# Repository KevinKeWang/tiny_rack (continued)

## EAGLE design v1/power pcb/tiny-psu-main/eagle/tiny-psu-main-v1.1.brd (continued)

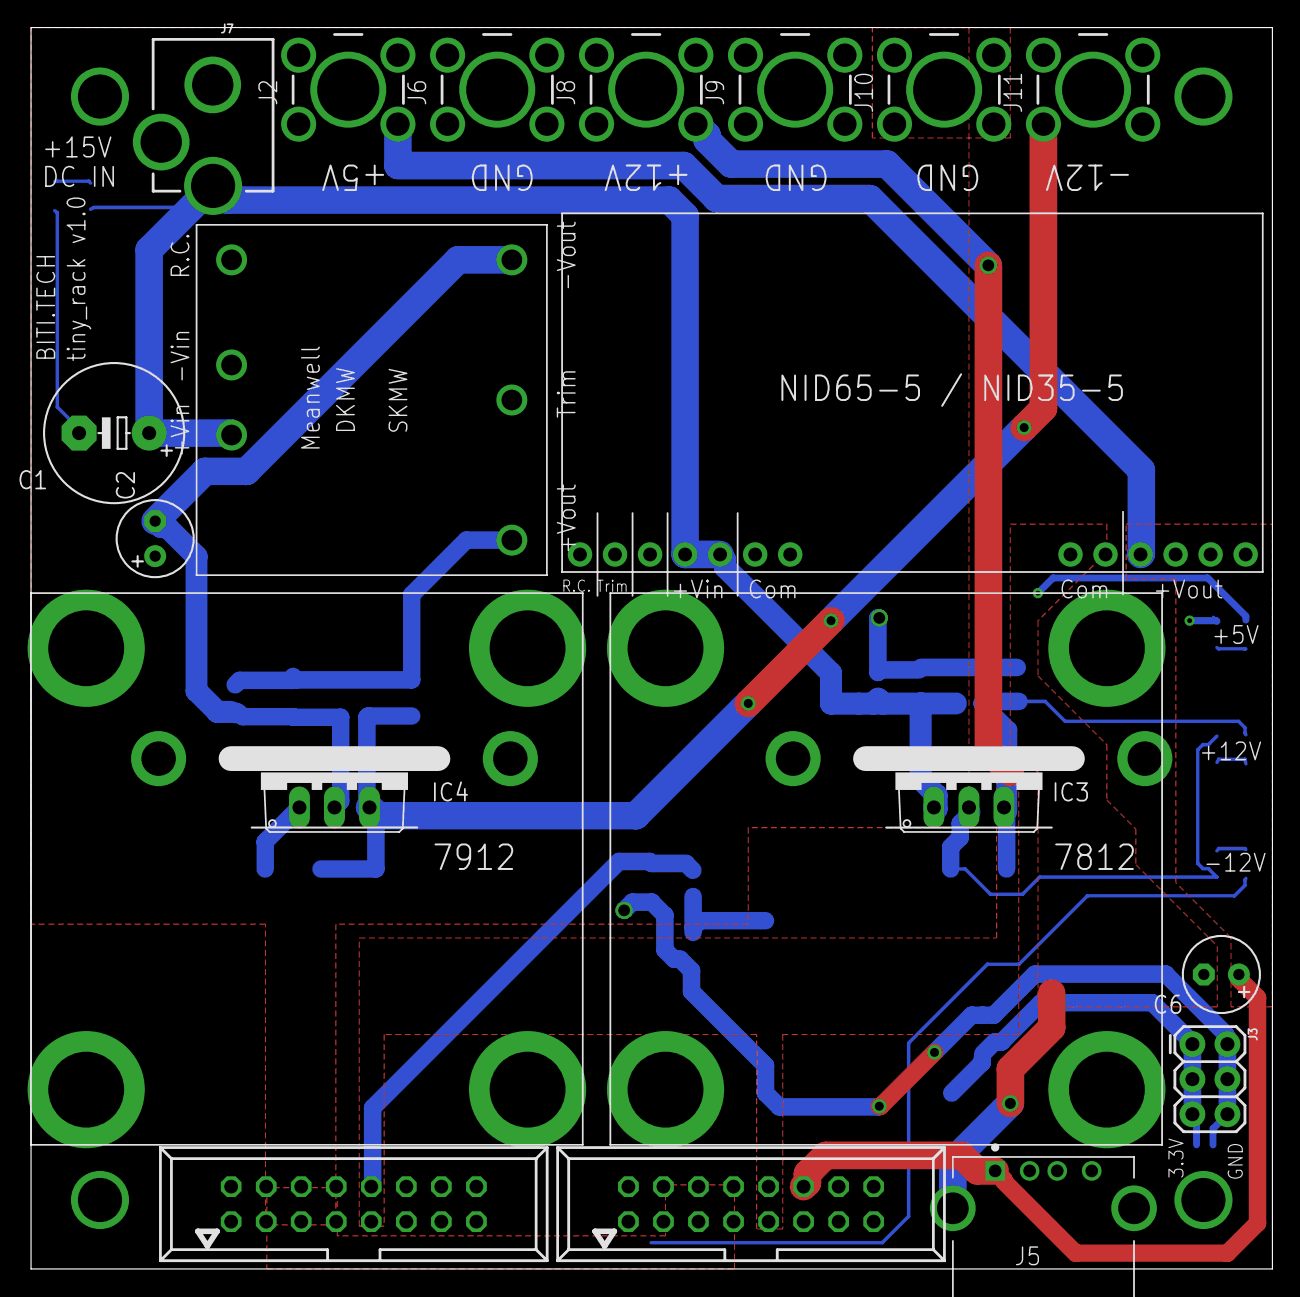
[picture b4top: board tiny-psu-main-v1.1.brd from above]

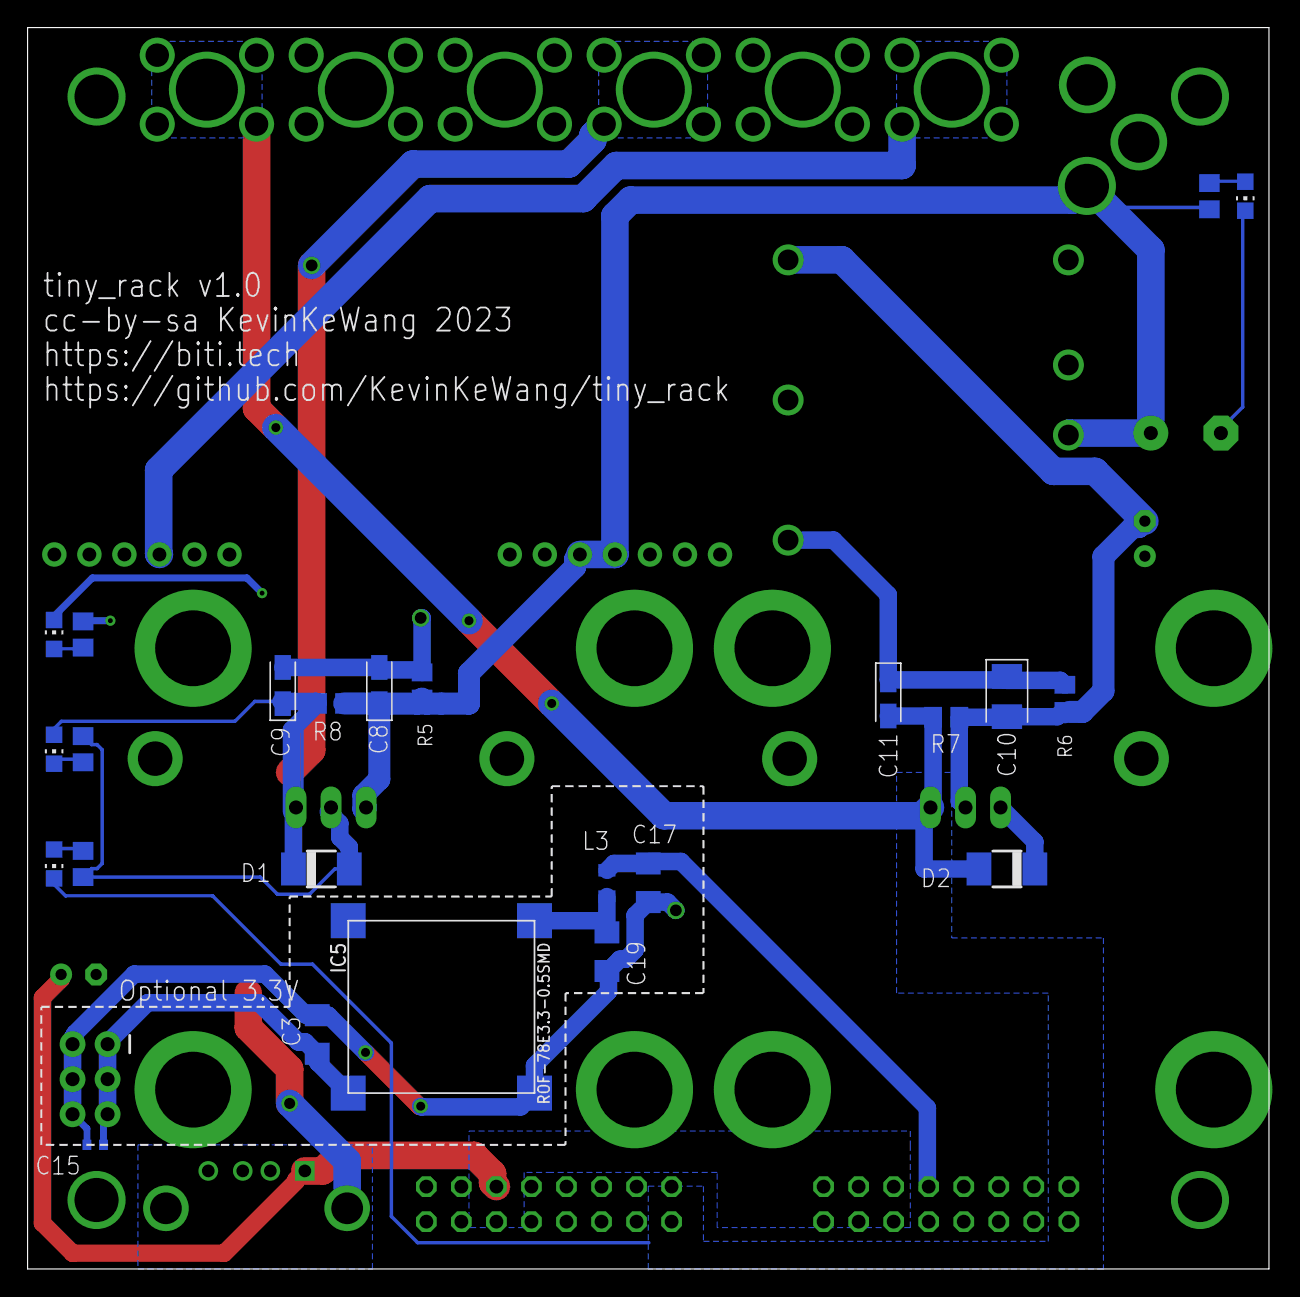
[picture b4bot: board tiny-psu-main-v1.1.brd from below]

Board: 4 copper layers, 90.0 x 90.0 mm, 46 parts (24 on the bottom side), 12 nets.

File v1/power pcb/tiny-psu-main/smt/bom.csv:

Comment,Designator,Footprint,jlc-partNo
LED,"LED1, LED2, LED3, LED4",0805,C2987021
1.2k,R3,0805,C17379
2.4k,"R1, R2, R4, R5, R6",0805,C17526
510R,"R7, R8",0805,C17734
100nF,C15,0402,C307331
22uF,"C3, C17, C19",1206,C12891
100nF,C9,CAPMP3216X180N,C7173
330nF,C8,CAPMP3216X180N,C8014
1uF,C11,CAPMP3216X180N,C7176
2.2uF,C10,CAPMP3528X210N,C19276
B360A-13-F,"D1, D2",DO-214AC,C94193
33uH,L3,L2012C,C383405

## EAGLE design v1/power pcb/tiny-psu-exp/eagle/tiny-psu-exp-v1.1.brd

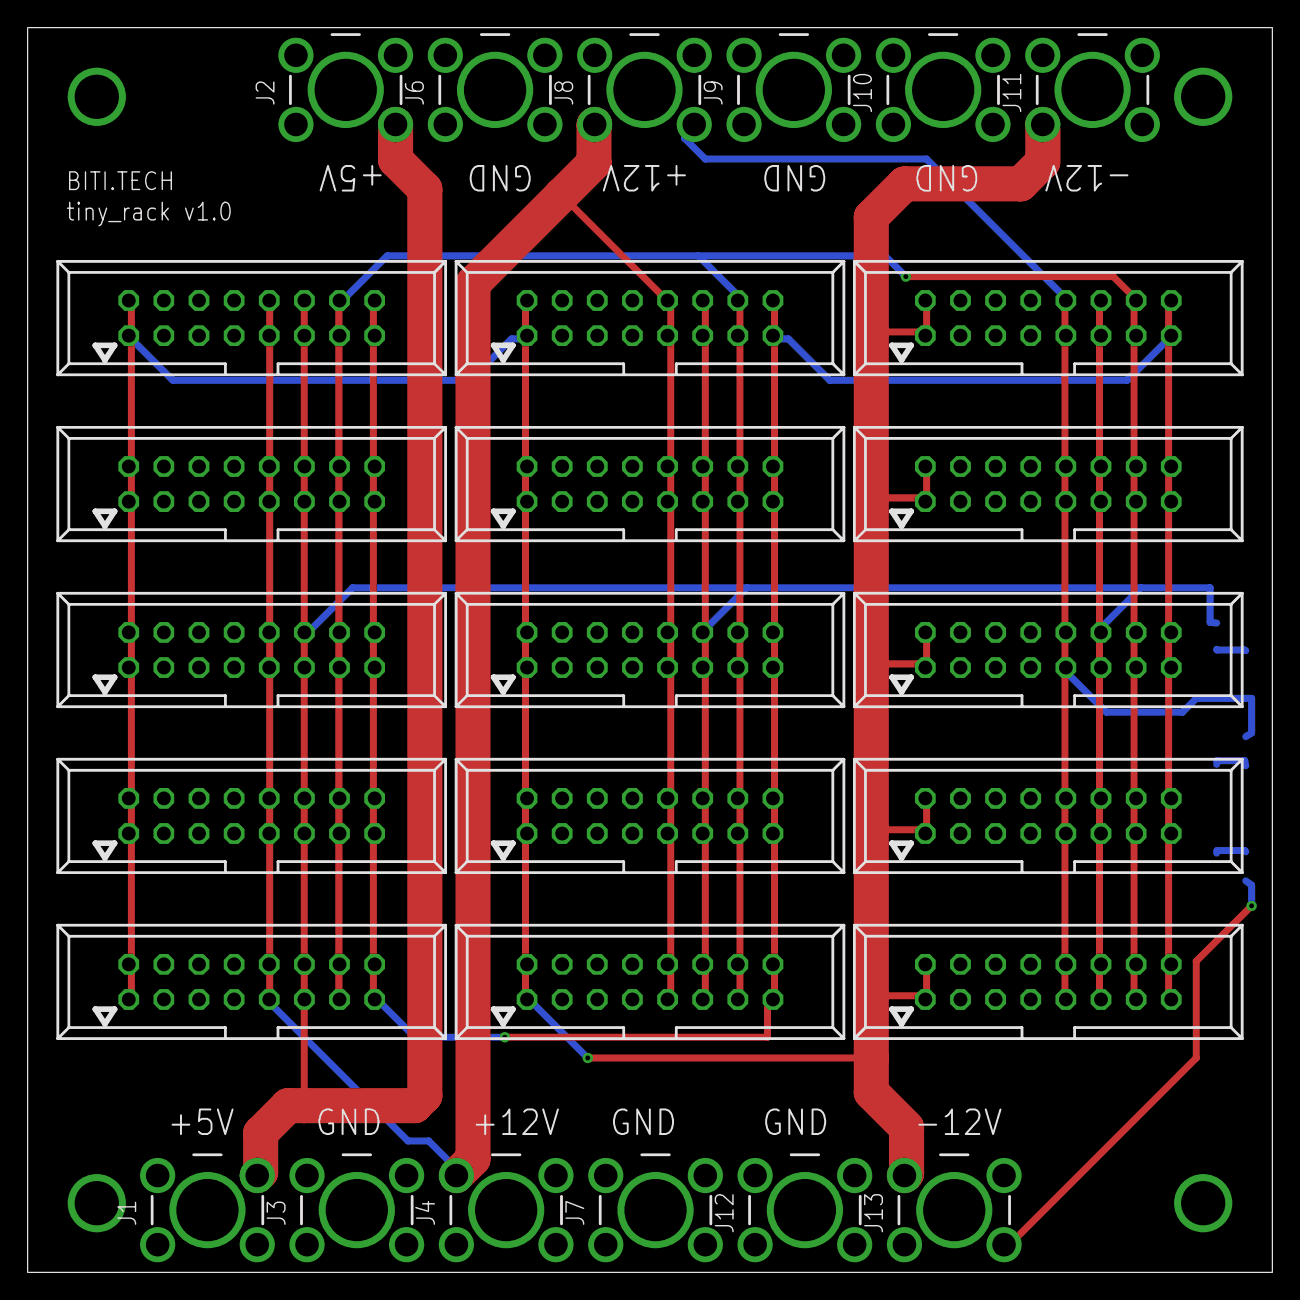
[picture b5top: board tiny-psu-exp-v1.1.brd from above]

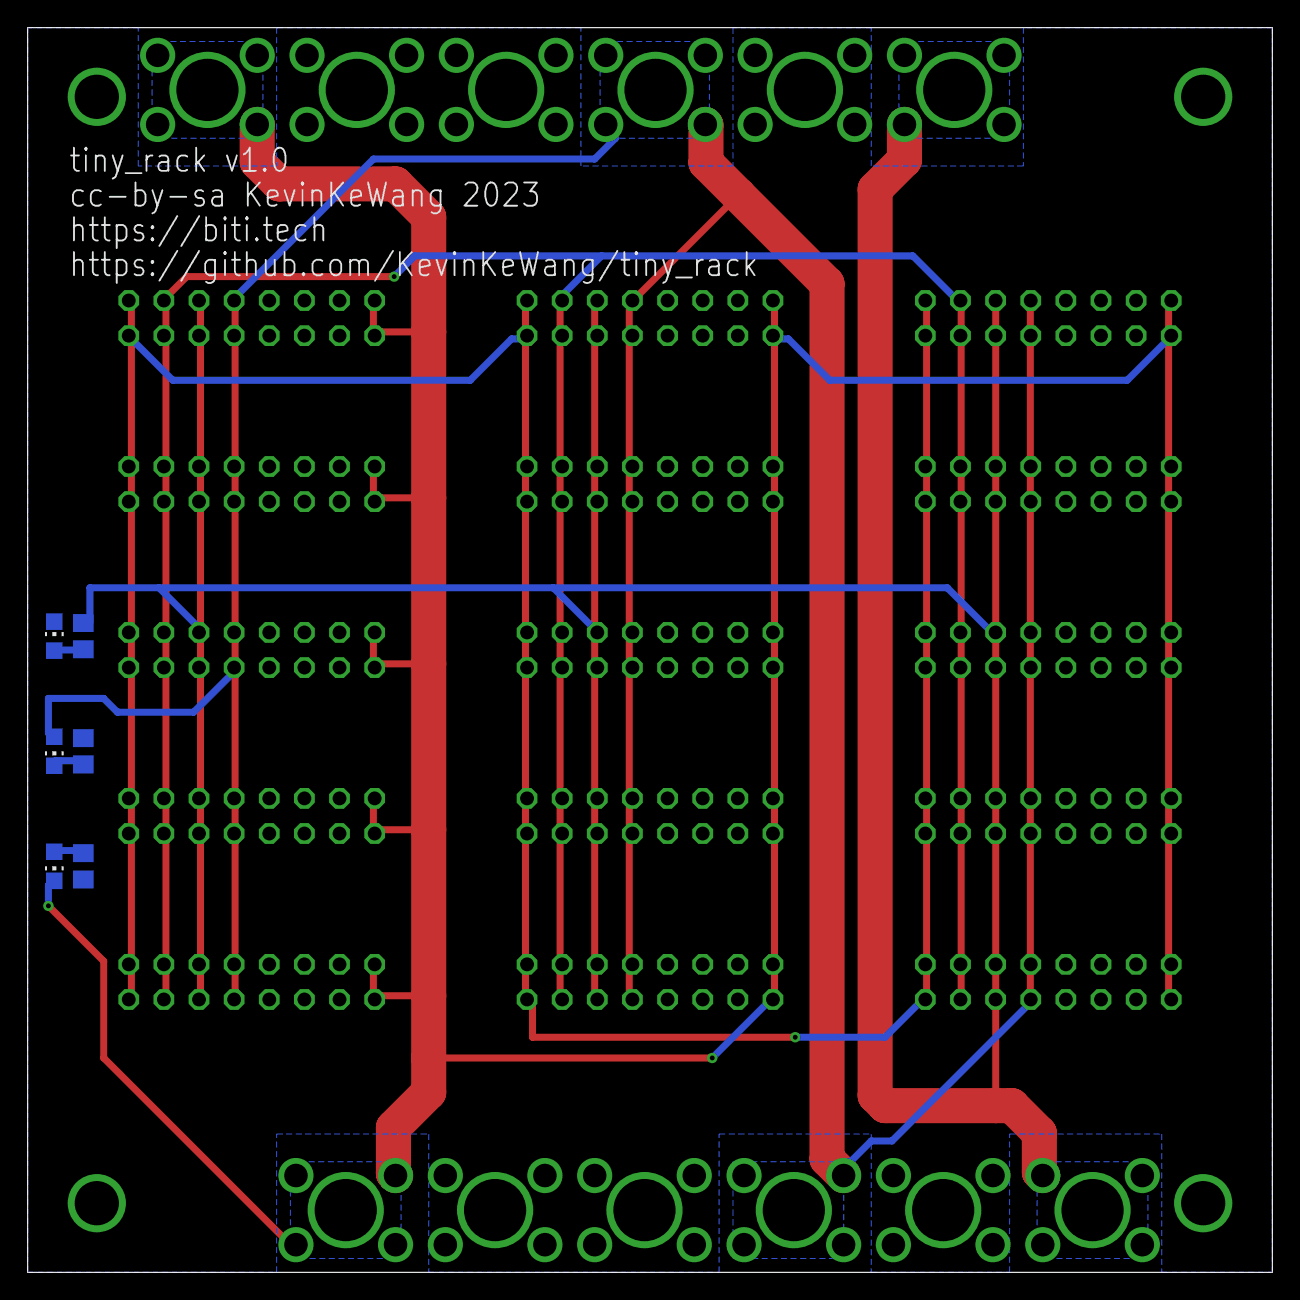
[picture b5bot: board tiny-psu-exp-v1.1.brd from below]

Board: 4 copper layers, 90.0 x 90.0 mm, 33 parts (6 on the bottom side), 9 nets.

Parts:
J1, J2, J3, J4, J6, J7, J8, J9, J10, J11, J12, J13: 30A-SCREW-CONN; 50X72
LED2, LED3, LED4: CHIP-LED0805
R1, R2: 2.4k; R0805
R3: 1.2k; R0805
X1, X4, X5, X6, X7, X8, X9, X10, X11, X13, X15, X17, X18, X19, X20: 057-016-10; 057-016-1

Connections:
+5V: J1.1, J1.2, J1.3, J1.4, J1.P$1, J2.1, J2.2, J2.3, J2.4, J2.P$1, R3.1, X1.11, X1.12, X4.11, X4.12, X5.11, X5.12, X6.11, X6.12, X7.11, X7.12, X8.11, X8.12, X9.11, X9.12, X10.11, X10.12, X11.11, X11.12, X13.11, X13.12, X15.11, X15.12, X17.11, X17.12, X18.11, X18.12, X19.11, X19.12, X20.11, X20.12
+12V: J4.1, J4.2, J4.3, J4.4, J4.P$1, J8.1, J8.2, J8.3, J8.4, J8.P$1, LED4.A, X1.9, X1.10, X4.9, X4.10, X5.9, X5.10, X6.9, X6.10, X7.9, X7.10, X8.9, X8.10, X9.9, X9.10, X10.9, X10.10, X11.9, X11.10, X13.9, X13.10, X15.9, X15.10, X17.9, X17.10, X18.9, X18.10, X19.9, X19.10, X20.9, X20.10
-12V: J11.1, J11.2, J11.3, J11.4, J11.P$1, J13.1, J13.2, J13.3, J13.4, J13.P$1, LED3.C, X1.1, X1.2, X4.1, X4.2, X5.1, X5.2, X6.1, X6.2, X7.1, X7.2, X8.1, X8.2, X9.1, X9.2, X10.1, X10.2, X11.1, X11.2, X13.1, X13.2, X15.1, X15.2, X17.1, X17.2, X18.1, X18.2, X19.1, X19.2, X20.1, X20.2
CV1: X1.13, X1.14, X4.13, X4.14, X5.13, X5.14, X6.13, X6.14, X7.13, X7.14, X8.13, X8.14, X9.13, X9.14, X10.13, X10.14, X11.13, X11.14, X13.13, X13.14, X15.13, X15.14, X17.13, X17.14, X18.13, X18.14, X19.13, X19.14, X20.13, X20.14
GATE1: X1.15, X1.16, X4.15, X4.16, X5.15, X5.16, X6.15, X6.16, X7.15, X7.16, X8.15, X8.16, X9.15, X9.16, X10.15, X10.16, X11.15, X11.16, X13.15, X13.16, X15.15, X15.16, X17.15, X17.16, X18.15, X18.16, X19.15, X19.16, X20.15, X20.16
GND: J3.1, J3.2, J3.3, J3.4, J3.P$1, J6.1, J6.2, J6.3, J6.4, J6.P$1, J7.1, J7.2, J7.3, J7.4, J7.P$1, J9.1, J9.2, J9.3, J9.4, J9.P$1, J10.1, J10.2, J10.3, J10.4, J10.P$1, J12.1, J12.2, J12.3, J12.4, J12.P$1, LED2.C, R1.2, R2.1, X1.3, X1.4, X1.5, X1.6, X1.7, X1.8, X4.3, X4.4, X4.5, X4.6, X4.7, X4.8, X5.3, X5.4, X5.5, X5.6, X5.7, X5.8, X6.3, X6.4, X6.5, X6.6, X6.7, X6.8, X7.3, X7.4, X7.5, X7.6, X7.7, X7.8, X8.3, X8.4, X8.5, X8.6, X8.7, X8.8, X9.3, X9.4, X9.5, X9.6, X9.7, X9.8, X10.3, X10.4, X10.5, X10.6, X10.7, X10.8, X11.3, X11.4, X11.5, X11.6, X11.7, X11.8, X13.3, X13.4, X13.5, X13.6, X13.7, X13.8, X15.3, X15.4, X15.5, X15.6, X15.7, X15.8, X17.3, X17.4, X17.5, X17.6, X17.7, X17.8, X18.3, X18.4, X18.5, X18.6, X18.7, X18.8, X19.3, X19.4, X19.5, X19.6, X19.7, X19.8, X20.3, X20.4, X20.5, X20.6, X20.7, X20.8
unnamed: LED4.C, R1.1
unnamed: LED3.A, R2.2
unnamed: LED2.A, R3.2

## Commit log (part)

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2023-10-21 init
2023-10-22 upload image
2023-10-22 test
2023-10-23 change image
2023-10-23 more pics
2023-10-24 add stl files
2023-10-24 update LICENSE
2023-10-24 更新 README.md
2023-10-24 more image
2023-10-27 add image
2023-10-29 update test report
2023-10-29 update power bank support
2023-10-29 update power bank test report
2023-10-29 update readme for power bank
2023-11-02 add 3D Print Instructions
2023-11-06 update gcode
2023-11-07 add gcode
2023-11-07 update 3d print instructions
2023-11-07 update 3d print gcode
2023-11-10 optimize 3d printing support
2023-11-11 add gcode for petg
2023-11-21 add reverb link
2024-09-09 joke
2024-09-13 fix mount issue
2025-04-16 update links
2025-04-21 v2 init
2025-04-21 images
2025-04-21 update images
2025-04-21 update doc
2025-04-22 update 3d model
2025-04-22 fix gcode and update image
2025-05-01 remove untest gcode
2025-05-07 add images
2025-07-19 add gerber file
2026-02-11 fix 3mf file
